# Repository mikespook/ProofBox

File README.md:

# TinyProofBox

An Arduino Nano based, (TODO: TinyGo implemented) sourdough proof box with LCD display

# Tools

[FreeCAD][freecad]
[KiCAD][kicad]
[Arduino IDE][ide]
TODO: [TinyGo][tinygo]

# Parts

[Arduino Nano][nano]
[DHT11][dht11] sensor
[LCD1602][lcd1602] with I2C adaptor
2 channel relay module
12V 40W Heater (diameter: 6mm, length: 20mm)
12V 4010 cooling fan
Heat sink (length: 36mm, height: 36mm, width: 35)
Prototype board (length: 70mm, width: 50mm)

[freecad]: https://www.freecadweb.org
[kicad]: https://www.kicad.org
[tinygo]: https://tinygo.org
[dht11]: https://create.arduino.cc/projecthub/search?q=DHT11
[lcd1602]: https://create.arduino.cc/projecthub/search?q=lcd1602+i2c
[nano]: https://www.arduino.cc/en/pmwiki.php?n=Main/ArduinoBoardNano
[ide]: https://www.arduino.cc/en/software

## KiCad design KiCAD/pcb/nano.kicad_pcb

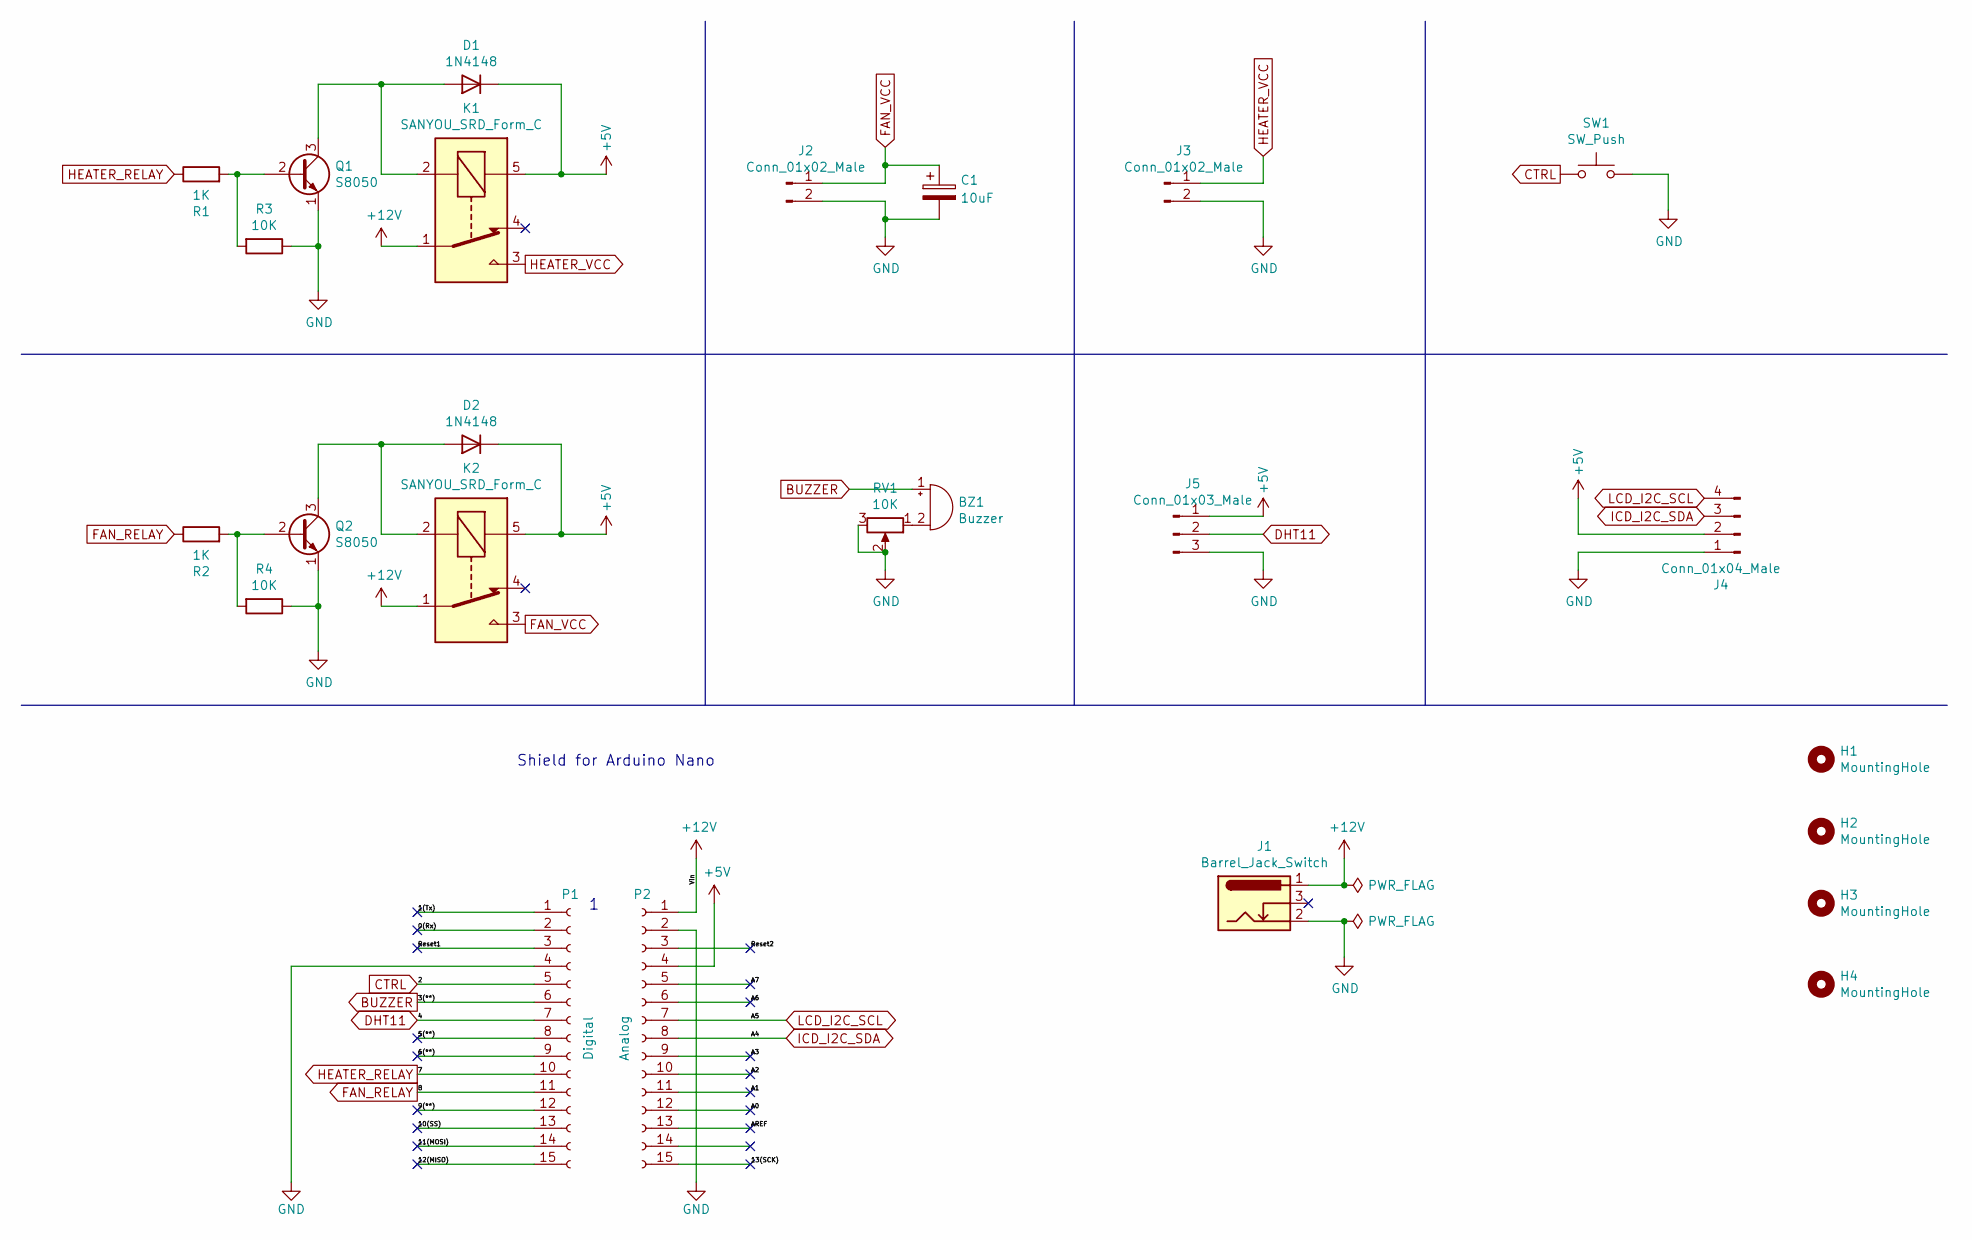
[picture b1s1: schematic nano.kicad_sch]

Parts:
BZ1: Buzzer; Buzzer_12x9.5RM7.6
C1: 10uF; CP_Radial_D5.0mm_P2.00mm
D1, D2: 1N4148; D_DO-35_SOD27_P7.62mm_Horizontal
H1, H2, H3, H4: MountingHole; MountingHole_2.2mm_M2
J1: Barrel_Jack_Switch; BarrelJack_Horizontal
J2, J3: Conn_01x02_Male; JST_XH_B2B-XH-AM_1x02_P2.50mm_Vertical
J4: Conn_01x04_Male; PinHeader_1x04_P2.54mm_Vertical
J5: Conn_01x03_Male; PinHeader_1x03_P2.54mm_Vertical
K1, K2: SANYOU_SRD_Form_C; Relay_SPDT_SANYOU_SRD_Series_Form_C
P1: Digital; PinSocket_1x15_P2.54mm_Vertical
P2: Analog; PinSocket_1x15_P2.54mm_Vertical
Q1, Q2: S8050; TO-92_Inline
R1, R2: 1K; R_Axial_DIN0204_L3.6mm_D1.6mm_P7.62mm_Horizontal
R3, R4: 10K; R_Axial_DIN0204_L3.6mm_D1.6mm_P7.62mm_Horizontal
RV1: 10K; Potentiometer_Runtron_RM-065_Vertical
SW1: SW_Push; SW_PUSH_6mm

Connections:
+5V: D1.1 (K), D2.1 (K), J4.2, J5.1, K1.5, K2.5, P2.4
+12V: J1.1, K1.1, K2.1, P2.1
/0(Rx): P1.2
/1(Tx): P1.1
/5(**): P1.8
/6(**): P1.9
/9(**): P1.12
/10(SS): P1.13
/11(MOSI): P1.14
/12(MISO): P1.15
/13(SCK): P2.15
/A0: P2.12
/A1: P2.11
/A2: P2.10
/A3: P2.9
/A6: P2.6
/A7: P2.5
/AREF: P2.13
/Reset1: P1.3
/Reset2: P2.3
BUZZER: BZ1.1 (-), P1.6
CTRL: P1.5, SW1.1
DHT11: J5.2, P1.7
FAN_RELAY: P1.11, R2.1
FAN_VCC: C1.1, J2.1, K2.3
GND: C1.2, J1.2, J2.2, J3.2, J4.1, J5.3, P1.4, P2.2, Q1.1 (E), Q2.1 (E), R3.1, R4.1, RV1.2, RV1.3, SW1.2
HEATER_RELAY: P1.10, R1.1
HEATER_VCC: J3.1, K1.3
ICD_I2C_SDA: J4.3, P2.8
LCD_I2C_SCL: J4.4, P2.7
unnamed: BZ1.2 (+), RV1.1
unnamed: D1.2 (A), K1.2, Q1.3 (C)
unnamed: D2.2 (A), K2.2, Q2.3 (C)
unnamed: Q1.2 (B), R1.2, R3.2
unnamed: Q2.2 (B), R2.2, R4.2

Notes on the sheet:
Shield for Arduino Nano

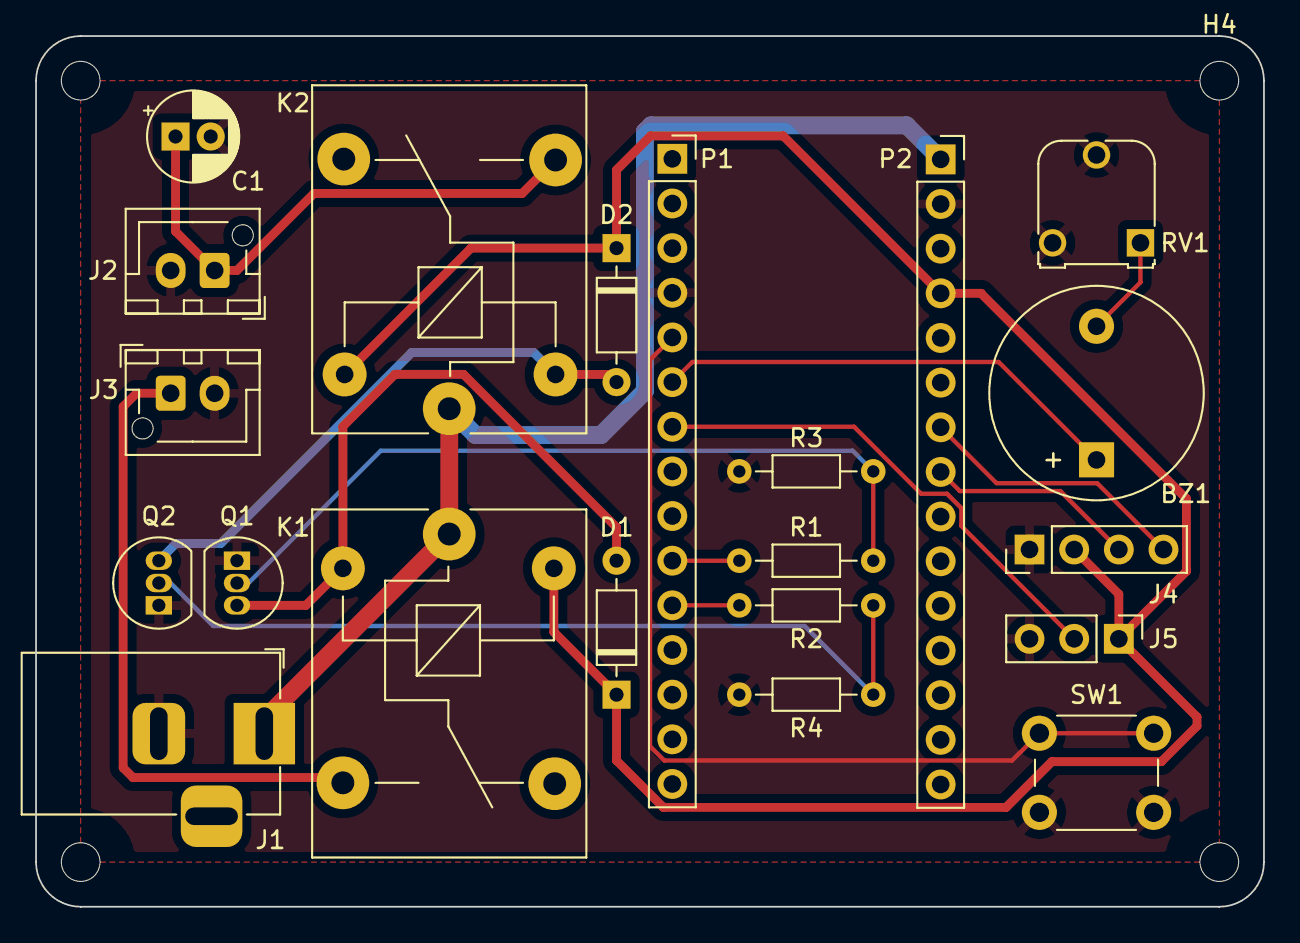
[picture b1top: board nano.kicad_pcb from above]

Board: 2 copper layers, 69.8 x 49.5 mm, 25 parts (0 on the bottom side), 17 nets.

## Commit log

2021-05-18 added parts
2021-05-19 update LCD stand
2021-05-19 try tinygo first
2021-05-25 heat sink & fan holders
2021-05-26 added base
2021-05-26 added assembled
2021-05-27 base design
2021-05-28 restructure base
2021-05-28 change module name
2021-05-28 blinky demo
2021-06-15 init arduino firmware
2021-06-23 added PCB board
2021-06-24 reroute wires
2021-06-24 split PCB and prototype board
2021-06-24 prototype board
2021-06-25 wires replaned
2021-09-15 button and buzzer
2021-09-15 added LCD
2021-09-15 debug info removed
2021-09-21 functional with kichiku
2021-09-21 fixed kichiku
2021-09-21 removed useless files
2022-02-17 upgrade to KiCAD 6
2022-02-28 fixed unlinked pads
2022-04-12 fixed display
2022-05-15 fixed LCD cable sequence
2022-05-15 PCB rearranged
2022-05-28 update 3D print housing
2022-06-01 added stands
2022-06-05 fixed logic of heating
2022-06-06 fixed fan off logic
2022-06-06 added button
2022-06-09 robust protection
2022-06-09 added capacitor to fan
2022-06-11 added watchdog
2022-06-11 better debug info
2022-06-11 remove useless condition
2022-06-11 fixed debug info
2022-06-11 added button holder
2022-06-11 on is the last step
2022-06-16 adjust tick of heating
2022-06-23 added pow func to have better temp rasing
2022-06-23 make sure fan off, heater off
2022-06-23 better params
2022-07-03 fixed reset error
2022-07-13 fixed watchdog reset on play sound
2023-08-02 21-22 is better for starter
2024-06-27 adjusted fan time

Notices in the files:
KiCAD/pcb/nano.kicad_pcb:
(C)2021-2022
